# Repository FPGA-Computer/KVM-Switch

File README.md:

KVM Switch
built from $5 HDMI switch + custom hardware

Details: https://hw-by-design.blogspot.com/2018/07/low-cost-kvm-switch.html

Hardware/ - Eagle CAD schematic, PCB, Sketchup 3D model (zipped)
Firmware/ - STM8S003 firmware source code for hotkey
KVM-Hotkey/ - initial test code I used during development.  
Included here for archive and completeiness because of my hosting changes.

Firmware written by me are licensed under GPL 3.0. 
Additional incorporated code are under their own licenses.

Hardware is licensed under CC BY-4.0

https://creativecommons.org/licenses/by/4.0/

Updates: change to Right CTRL key as hotkey.

Updates:

- Optional active or'ing circuit to replace Schottky diodes for lower voltage drops.

Or'ing circuit imspired by RPi 3 Model B rev. 1.2 USB power circuit. The matching transistor pair is
not needed - verified by simulation.  Voltage drop (roughly 50mV @0.5A). The circuit can share current
from multiple USB supplies.

- new USB Mux-v0.2 PCB layout with larger wiring pads, pads for optional or'ing circuit

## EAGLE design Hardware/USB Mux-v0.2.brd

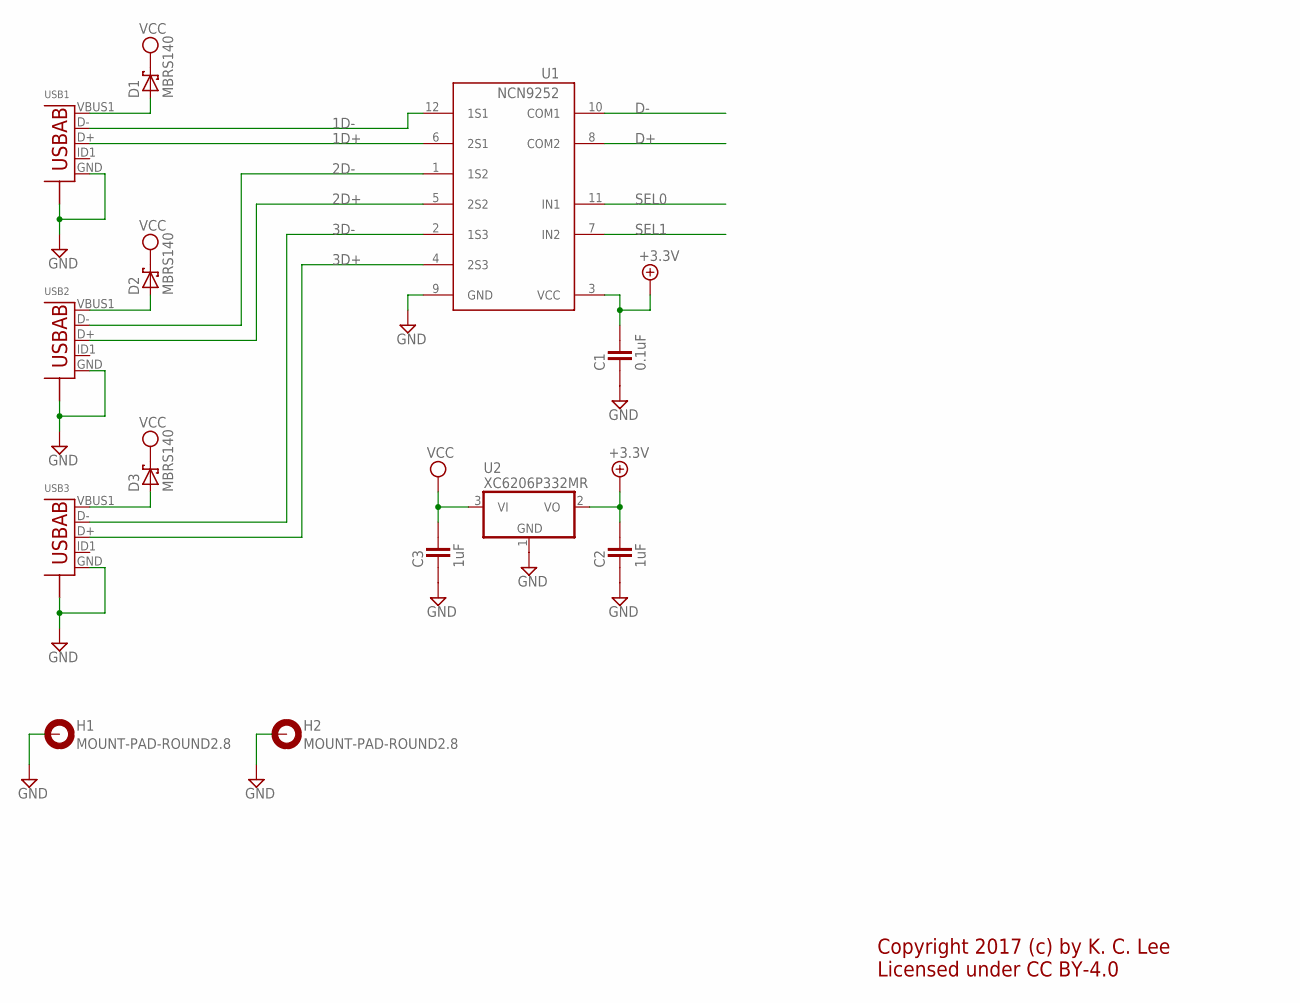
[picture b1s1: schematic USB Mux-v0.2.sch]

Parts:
C1: 0.1uF; CAPC1608X92N; PARTNO 0U1 0603
C2, C3: 1uF; CAPC1608X92N; PARTNO 1UF 0603
D1, D2, D3: MBRS140; DIOM5436X265N; PARTNO MBRS140
H1, H2: MOUNT-PAD-ROUND2.8; 2,8-PAD; PARTNO *
U1: NCN9252; UQN12; PARTNO NCN9252
U2: XC6206P332MR; SOT95P280X135-3N; PARTNO XC6206P332MR
USB1, USB2, USB3: USB-ABBG-ORG; USB-AB-MICRO-SMD_V03_SMT; PARTNO SMT MICRO USB CONNECTOR

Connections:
1D+: U1.6 (2S1), USB1.D+
1D-: U1.12 (1S1), USB1.D-
2D+: U1.5 (2S2), USB2.D+
2D-: U1.1 (1S2), USB2.D-
3D+: U1.4 (2S3), USB3.D+
3D-: U1.2 (1S3), USB3.D-
+3.3V: C1.2, C2.2, U1.3 (VCC), U2.2 (VO)
D+: U1.8 (COM2)
D-: U1.10 (COM1)
GND: C1.1, C2.1, C3.1, H1.B2,8, H2.B2,8, U1.9 (GND), U2.1 (GND), USB1.GND, USB1.S1 (S), USB1.S2 (S), USB1.S3 (S), USB1.S4 (S), USB2.GND, USB2.S1 (S), USB2.S2 (S), USB2.S3 (S), USB2.S4 (S), USB3.GND, USB3.S1 (S), USB3.S2 (S), USB3.S3 (S), USB3.S4 (S)
unnamed: D3.A, USB3.VBUS1 (VBUS)
unnamed: D2.A, USB2.VBUS1 (VBUS)
unnamed: D1.A, USB1.VBUS1 (VBUS)
SEL0: U1.11 (IN1)
SEL1: U1.7 (IN2)
VCC: C3.2, D1.K, D2.K, D3.K, U2.3 (VI)

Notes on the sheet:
Copyright 2017 (c) by K. C. Lee Licensed under CC BY-4.0

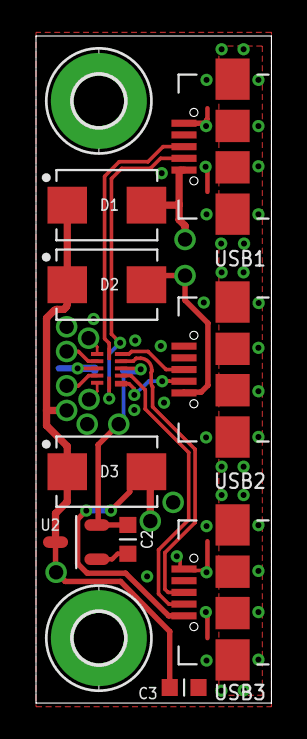
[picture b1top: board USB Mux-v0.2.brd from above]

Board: 2 copper layers, 13.1 x 37.1 mm, 13 parts (1 on the bottom side), 12 nets.

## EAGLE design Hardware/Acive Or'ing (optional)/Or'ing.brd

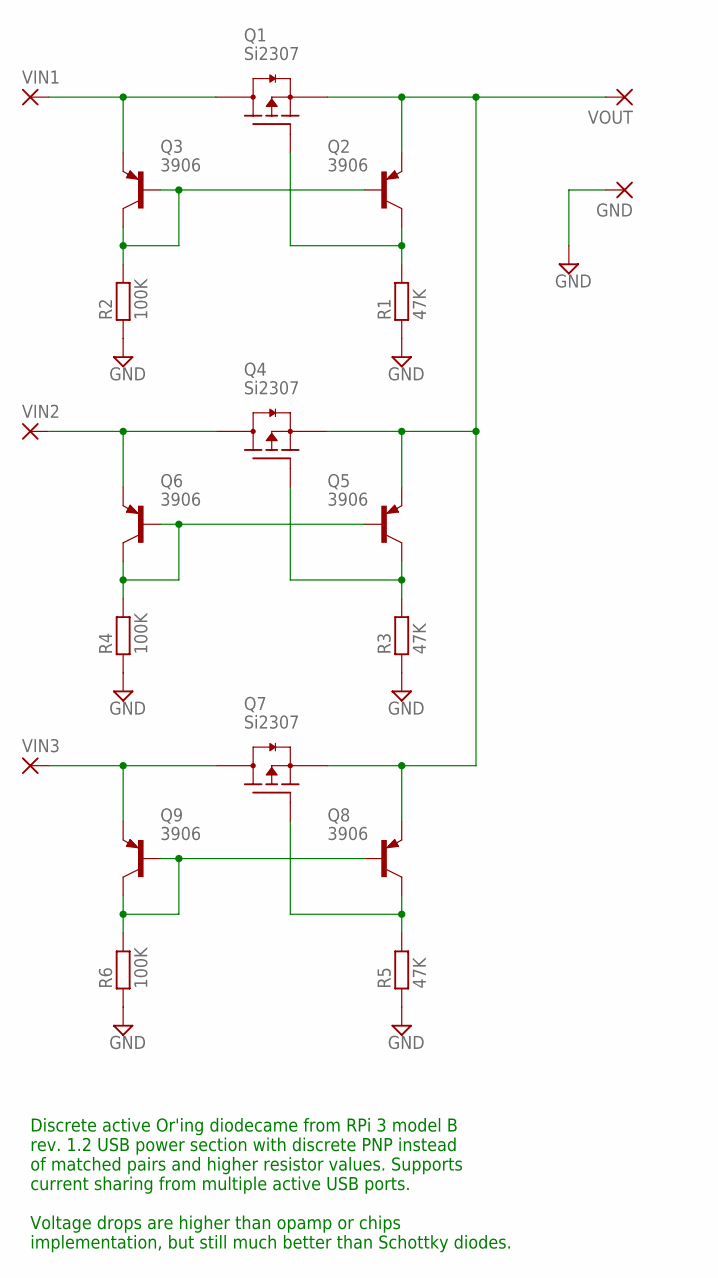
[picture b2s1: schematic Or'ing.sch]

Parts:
GND: SMD2; SMD1,27-2,54
Q1, Q4, Q7: Si2307; SOT95P280X135-3N
Q2, Q3, Q5, Q6, Q8, Q9: 3906; SOT95P280X135-3N
R1, R3, R5: 47K; RESC1608X55N
R2, R4, R6: 100K; RESC1608X55N
VIN1, VIN2, VIN3: SMD2; SMD1,27-2,54
VOUT: SMD2; SMD1,27-2,54

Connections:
GND: GND.1, R1.1, R2.1, R3.1, R4.1, R5.1, R6.1
unnamed: Q1.2 (S), Q2.2 (E), Q4.2 (S), Q5.2 (E), Q7.2 (S), Q8.2 (E), VOUT.1
unnamed: Q1.3 (D), Q3.2 (E), VIN1.1
unnamed: Q1.1 (G), Q2.3 (C), R1.2
unnamed: Q2.1 (B), Q3.1 (B), Q3.3 (C), R2.2
unnamed: Q4.3 (D), Q6.2 (E), VIN2.1
unnamed: Q4.1 (G), Q5.3 (C), R3.2
unnamed: Q5.1 (B), Q6.1 (B), Q6.3 (C), R4.2
unnamed: Q7.3 (D), Q9.2 (E), VIN3.1
unnamed: Q7.1 (G), Q8.3 (C), R5.2
unnamed: Q8.1 (B), Q9.1 (B), Q9.3 (C), R6.2

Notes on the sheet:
Discrete active Or'ing diodecame from RPi 3 model B rev. 1.2 USB power section with discrete PNP instead of matched pairs and higher resistor values. Supports current sharing from multiple active USB ports. Voltage drops are higher than opamp or chips implementation, but still much better than Scho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

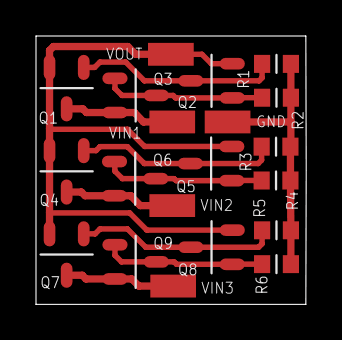
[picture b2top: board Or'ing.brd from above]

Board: 2 copper layers, 15.0 x 14.9 mm, 20 parts (0 on the bottom side), 11 nets.

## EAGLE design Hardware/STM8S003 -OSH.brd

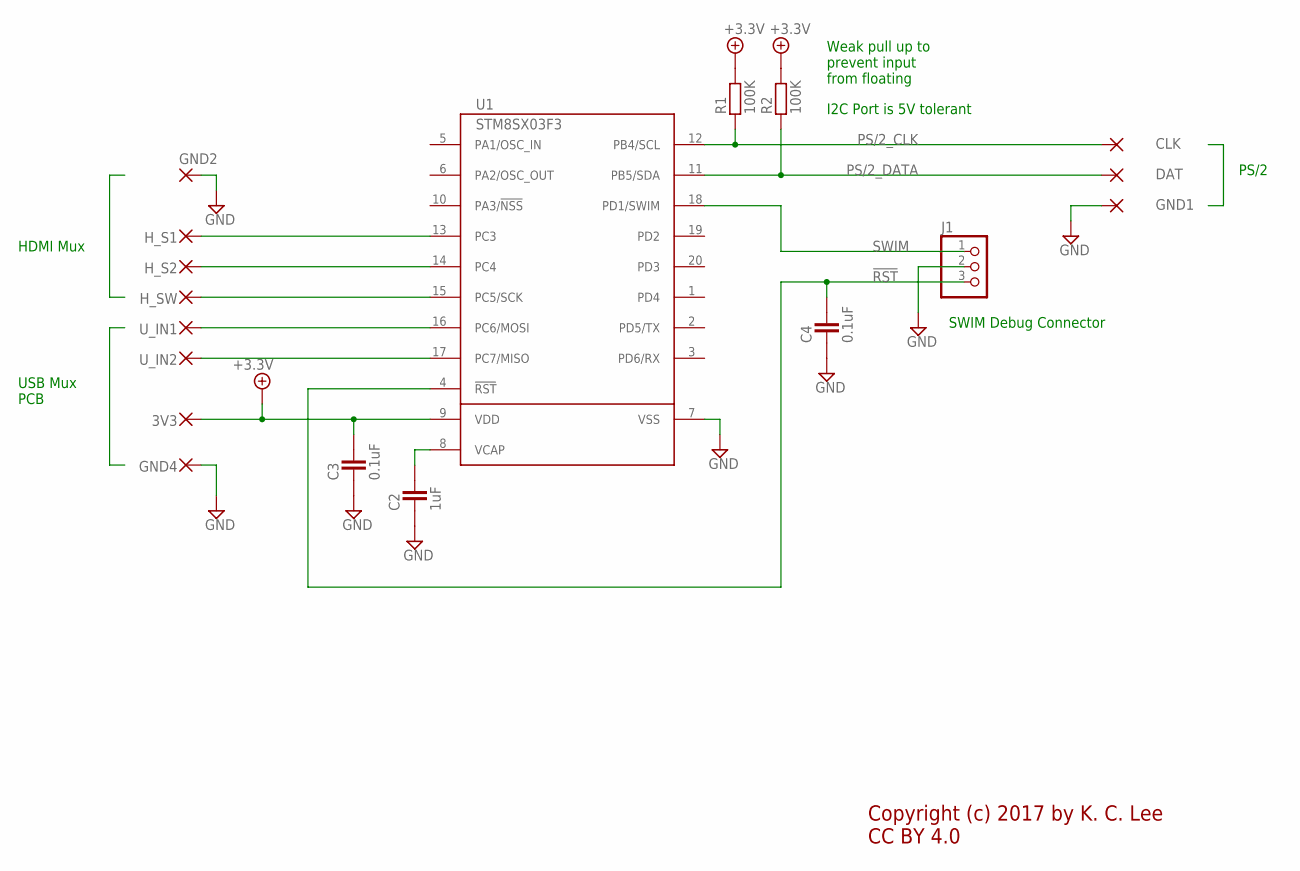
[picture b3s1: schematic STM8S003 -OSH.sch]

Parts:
3V3: SMD2; SMD1,27-2,54
C2: 1uF; CAPC1608X92N
C3, C4: 0.1uF; CAPC1608X92N
CLK: SMD2; SMD1,27-2,54
DAT: SMD2; SMD1,27-2,54
GND1, GND2, GND4: SMD2; SMD1,27-2,54
H_S1, H_S2: SMD2; SMD1,27-2,54
H_SW: SMD2; SMD1,27-2,54
J1: PINHD-1X3; 1X03
R1, R2: 100K; RESC1608X55N
U1: STM8SX03F3; TSSOP20
U_IN1, U_IN2: SMD2; SMD1,27-2,54

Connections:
!RST: C4.2, J1.3, U1.4 (!RST)
+3.3V: 3V3.1, C3.2, R1.2, R2.2, U1.9 (VDD)
GND: C2.1, C3.1, C4.1, GND1.1, GND2.1, GND4.1, J1.2, U1.7 (VSS)
unnamed: C2.2, U1.8 (VCAP)
unnamed: U1.17 (PC7/MISO), U_IN2.1
unnamed: U1.16 (PC6/MOSI), U_IN1.1
unnamed: H_SW.1, U1.15 (PC5/SCK)
unnamed: H_S1.1, U1.13 (PC3)
unnamed: H_S2.1, U1.14 (PC4)
PS/2_CLK: CLK.1, R1.1, U1.12 (PB4/SCL)
PS/2_DATA: DAT.1, R2.1, U1.11 (PB5/SDA)
SWIM: J1.1, U1.18 (PD1/SWIM)

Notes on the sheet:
Copyright (c) 2017 by K. C. Lee CC BY 4.0
HDMI Mux
USB Mux PCB
PS/2
SWIM Debug Connector
Weak pull up to prevent input from floating
I2C Port is 5V tolerant

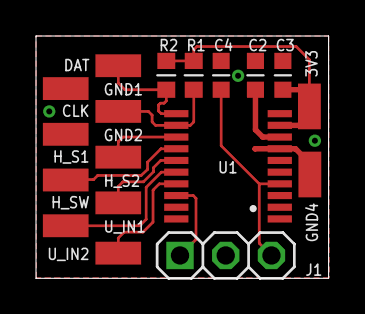
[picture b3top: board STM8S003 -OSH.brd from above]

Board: 2 copper layers, 16.3 x 13.5 mm, 18 parts (0 on the bottom side), 12 nets.

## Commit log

2017-04-28 Initial commit - PCB not tested
2017-08-15 Firmware added
2017-08-15 USB Select code cleanup
2017-08-25 Add delay for USB hotkey release before switching
2018-07-31 added AZHW371 datasheet - no longer listed on manufacturer's site
2018-07-31 Dead branch - Code used during development. Included here for archive due to hosting changes.
2019-06-10 Right CTRL as hotkey
2022-04-30 PCB update, optional or'ing circuit
2022-05-21 Add wiring diagram, pictures of PCB
